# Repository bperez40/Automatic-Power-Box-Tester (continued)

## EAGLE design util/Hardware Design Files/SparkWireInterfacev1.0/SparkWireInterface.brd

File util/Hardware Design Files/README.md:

# Hardware Guide
Originally, the power box tester was intended to be a single board to which you attach connectors to. Were it not for the 25 kV ignition, this would be possible. However, because we could not implement a part of the circuit on either the Auto Power Box Tester PCB or on the Spark Wire Interface board due to time limitations, the setup requires slightly more complexity and care.

## Auto Power Box Tester v1.1 Assembly
Setting up the Auto Power Box Tester v1.1 is very straightforward, though it does require a bit of soldering (though every part can be done with a soldering iron alone).

If you have no prior experience with soldering, here are a few guides on how to do so.

SMD soldering: https://www.sparkfun.com/tutorials/36
Through hole soldering: https://learn.sparkfun.com/tutorials/how-to-solder-through-hole-soldering/all#res
Hot air: https://learn.sparkfun.com/tutorials/how-to-use-a-hot-air-rework-station/all

Assemble the board in its entirety. Ideally, this board would be assembled by the PCB manufacturer, so for future revisions, consider getting this assembled by the manufacturer as it is more or less in a stable position. 

The connectors are also all assembled with each connection as is with the exception of the blower motor connector, which I will elaborate on later. Each of these connectors have a Mini-Fit Jr. receptacle on one end and a Mini-Fit Jr. panel mount plug on the other end.

The Spark Wire Interface board is a supplementary board to the main board. It required major adjustments after production, so this is where the complexity comes in.

First, start by assembling the required components of the spark interface board. Adjustments were made to exclude parts of the board, so you will only need to assemble:
- J1
- R3
- R4
- D1
- Quick connect tab on the holes labeled "spark wire connect"

After those are assembled, you will also need to place a jumper wire in one location, with the solder joints being circled in this image:\

As a result, it will look something like this:\

The idea here is we're trying to short the path that leads between the spark wire interface and the rectification circuit. Instead of that circuit being closed by a +3.3v relay (as it originally was supposed to be), it is being closed by a 120 VAC contactor. We had to change those out as the contactor could handle the higher voltage rating on its contacts (effectively, it prevented the high voltage line from arcing when in its open position due to the larger air gaps).

Now, we need to make a few connections. Terminal block for reference:\

Start by connecting the left most AGND to the interior of the chassis (requires a ring terminal crimp). Next, connect the right AGND to a wire nut. From that wire nut, you need to attach two more wires to two separate locations: One back to AGND OPT, and the other to one side of the contactor's coil (requires a quick connect crimp). The other side of the contactor's coil should be connected to wire 2 on the blower motor connector. That way, the contactor now has both 120 VAC and GND connected to its coil.

After the two boards are assembled properly, you'll need to make connections to the breadboard and contactor. Usually, the breadboard would be integrated onto the spark interface board, but since there wasn't enough time remaining in the internship to do so, we had to settle for this.

The breadboard is a corrected circuit of what the spark interface board should have been, and it requires the following
- NPN transistor (like the MPSA06): 1
- 270 ohm resistor: 1
- 3700 ohm resistor: 2
- [J104D2C3VDC.15S or equivalent 3.3v relay](https://www.digikey.com/en/products/detail/cit-relay-and-switch/J104D2C3VDC-15S/12502634)
- [CPC1976Y, AQY212GHAX, or something similar](https://www.digikey.com/en/products/detail/ixys-integrated-circuits-division/CPC1976Y/1277138)

Using these, you need to build the following circuit. Pay heed to the comments:\

To finish these connections, we need to connect the rest of the contactor's connections. We've already attached the necessary wires to the coil ends, but we need to set up the spark wire to connect to the terminal. One side of a terminal should by connected directly to the power box's spark wire (usually we connect the spark wire to a QC terminal on the workbench and have another wire leading into the Auto Power Box Tester's chassis, where it then connects to one of the contactor's terminal). The other side of that terminal should be connected to the quick connect labeled "SPARK WIRE CONNECT" on the spark wire interface board. After that, the device should be fully electrically assembled. You know this is done incorrectly if the device is never able to rectify the signal (no path to ground) or if there is arcing occuring between the AGND and AGND OPT traces (unequal potentials between these two signals).

Effectively, what all this was for was to allow the Arduino to be able to control when the spark wire's signal is being recitified or not. The circuit on the breadboard allows the Arduino to control a 120 VAC signal (on the pump motor connector's second wire), which in turn triggers the contactor on and off.

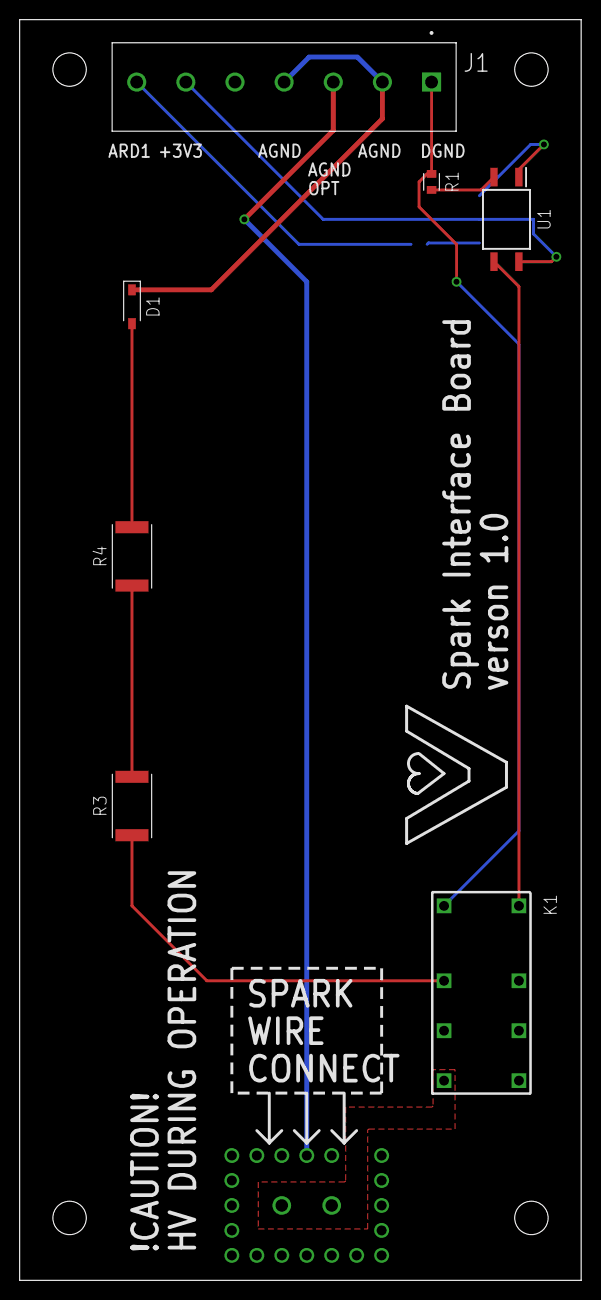
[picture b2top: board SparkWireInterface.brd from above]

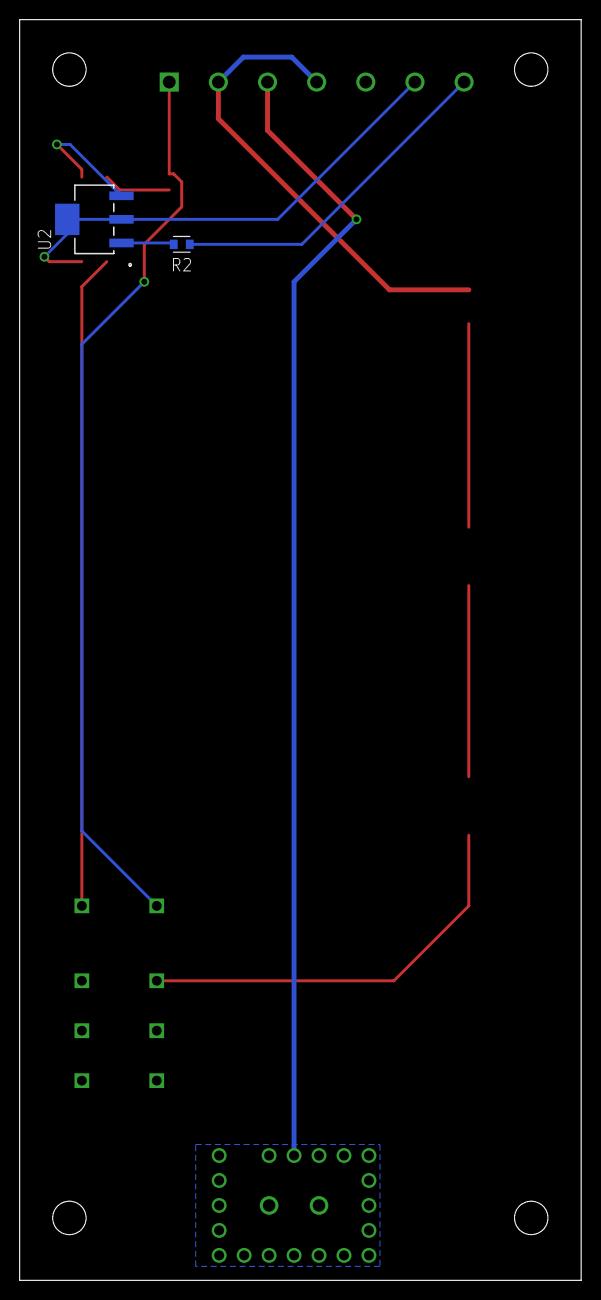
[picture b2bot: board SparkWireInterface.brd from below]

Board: 2 copper layers, 57.1 x 128.3 mm, 9 parts (2 on the bottom side), 11 nets.

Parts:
D1: 1N4148W; SOD3715X135
J1: TB001-500-07BE; CUI_TB001-500-07BE
K1: J104D2C3VDC.15S
R1: 330; RESC1608X60
R2: 3300; RESC1608X60
R3, R4: 10M; RESC6332X71
U1: AQY212GHAX; SOP254P962X315-4N
U2: PZTA06SOT-223_ONS; SOT-223_ONS

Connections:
+3V3: J1.6, U1.4, U2.2, U2.4
AGND2: D1.1, J1.2, J1.4
ARD1: J1.7, R2.1
DGND: J1.1, K1.1, R1.1
unnamed: K1.2, U1.3
unnamed: U1.1, U2.3
unnamed: R1.2, U1.2
unnamed: R2.2, U2.1
unnamed: K1.3, R3.1
unnamed: R3.2, R4.1
unnamed: D1.2, R4.2

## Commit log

2022-06-09 Update pwmReadStarter.ino
    Removed linked lists in favor of arrays stored in memory
2022-06-09 Fixed again, but with linked lists
2022-06-10 Added take two
2022-06-10 Functioning sampling and duty cycle calculation. For whatever reason bugged when other arduino outputs higher duty cycles
2022-06-10 added leniency
2022-06-15 Added initial libraries
2022-06-15 Added more
2022-06-15 added stuff
2022-06-15 removed .vscode
2022-06-15 stuff
2022-06-15 gitignore modified
2022-06-15 fixed
2022-06-15 gitignore update
2022-06-15 docs update
2022-06-15 docs
2022-06-15 added visualizer
2022-06-15 Added iodefs
2022-06-16 Added python virtual environment
2022-06-16 Removed that shtuff
2022-06-16 updated gitignore
2022-06-17 updated readme and visualizer
2022-06-17 removed excel file
2022-06-17 Added ADC test
2022-06-17 Added visualization with logging
2022-06-17 Fixed visualizer
2022-06-17 Updated everything
2022-06-17 Created library for PBT Check
2022-06-17 Autoformat
2022-06-17 Standardized PBTCheck
2022-06-17 Changed something idk
2022-06-20 Library for PBT check fixed
2022-06-20 Added Adafruit RA8875 library as submodule
2022-06-20 Added submodule prt 2
2022-06-20 Reorganized library
2022-06-20 I'm stuff
2022-06-20 Readme updates
2022-06-20 assests
2022-06-21 Everything starting display and user interaction
2022-06-21 a lot of menu additions and organization
2022-06-30 Adjusted menu, added results menu
2022-06-30 Exit box stuff
2022-06-30 Can switch between main, pre, post , and results
2022-06-30 Adding to tests
2022-06-30 Added ordering info
2022-06-30 iodefs cpp change
2022-06-30 filter test stuff
2022-06-30 iodef changes and started on PIM info screen
2022-07-01 Running out of static memory soon
2022-07-01 Added basket test box and optimizations
2022-07-01 Optimizations
2022-07-01 Added test status'
2022-07-01 More signal detection added
2022-07-01 PIM Info page updated
2022-07-05 Added high and low duty cycle checks
2022-07-05 Adjusting pwm testing tools
2022-07-05 Adjusted tests and added option for avg duty calc
2022-07-05 Fixed pwmCheck
2022-07-05 Added test progress messages
2022-07-05 Basic info screen functions implemented
2022-07-05 graphed duty cycle option proven to work
2022-07-05 Removing unecessary serial statements
2022-07-05 Added gitignore for build files
2022-07-05 Added title boxes in info screens
2022-07-06 Adjusted setup script
2022-07-06 Added openocd via msys2 but debug not supported :(
2022-07-06 Stuffs
2022-07-06 Updated readme and setup script
2022-07-06 Added touch rejection
2022-07-06 Adjusted recommendations box
2022-07-06 Decorations
2022-07-11 Better setup script and edited readme
2022-07-11 Readme adjusted again
2022-07-11 added stuffs
2022-07-13 Abort safety feature added
2022-07-20 Added revision for Auto Power Box Tester
2022-07-20 Previous commit but actually
2022-07-21 Updated readme and ordering info
2022-07-22 Moved graphics functions to seperate library
2022-07-22 Seperated graphics functions into their own lib
2022-07-22 Adjusted menus
2022-07-25 Configuration setting now stored in EEPROM
2022-07-25 toggelable outputs in debug. Needs touch rejection
2022-07-25 Cool downs for buttons in debug
2022-07-26 Implemented touch rejection w/ cooldowns
2022-07-26 text now stays after button press
2022-07-26 Comments and added black outline around border
2022-07-26 Removed unnecessary heap allocation
2022-07-26 Power on status added to debug and non touch event
2022-07-26 Updated iodefs and working on debug menu
2022-07-26 Debug functional. Need to add power lockout
2022-07-27 Cleaning
2022-07-27 status on manual debug screen now update correctly
2022-07-27 Power lockout implemented into manual
2022-07-27 Adding flame sense button (only visual init)
2022-07-27 Added flame sense button to manual control
2022-07-27 Calibration
2022-07-28 removed recom, adjusted results for non filter
2022-07-28 Adjusted results button location
2022-07-28 Connections menu in progress
2022-07-28 Updated connections graphics
2022-07-28 Brought back safety feature
2022-07-29 Updated connections menu
2022-08-03 Converting connections menu into info menu
2022-08-03 Added sample and average functionality
2022-08-03 Functioning sampleAndAverage
2022-08-03 Adjusted auto test parameters and order
2022-08-04 pulled libraries
2022-08-04 Updating readme
2022-08-04 uploading image
2022-08-04 Updating readme and adding more images
2022-08-04 More readme updates
2022-08-04 rdme updates
2022-08-05 Added image
2022-08-05 Readme update
2022-08-05 Updated readme and file organization
2022-08-05 More reorganization
2022-08-05 Reorganization
2022-08-05 reorganization part 10 or whatever
2022-08-05 readme
2022-08-05 Better manual test, duty cycle check functions
2022-08-05 changed manual test to update pwm correctly
2022-08-08 Adjusted waitUntilTriggered to be more strict
2022-08-08 Added ability to lock manual mode
2022-08-08 bugfixes
2022-08-09 reorg
2022-08-09 Adjusted CompileAndUpload script
2022-08-09 ignoring putty.log
2022-08-09 Split scripts and readme update
2022-08-09 renamed images
2022-08-09 Fixed auto test
2022-08-09 actually fixed auto test
2022-08-09 Adjusted high duty cycle timing
2022-08-10 Alarm now checked during auto test
2022-08-10 formatting
